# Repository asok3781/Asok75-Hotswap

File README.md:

# Asok75v2-Hotswap
This is a PCB designed to fit in the TX75v2 and be a replacement PCB for this keyboard, integrating Kailh hotswap sockets into the board.

This PCB uses [QMK firmware](https://github.com/asok3781/qmk_firmware/tree/asok/keyboards/asok/asok75hs) and a [VIA definition](asok75hsViaDefinition) has also been created to easily customise the layout of the keyboard.

This PCB uses QMK compatible side-firing LEDs to keep the underglow of the original PCB bright.

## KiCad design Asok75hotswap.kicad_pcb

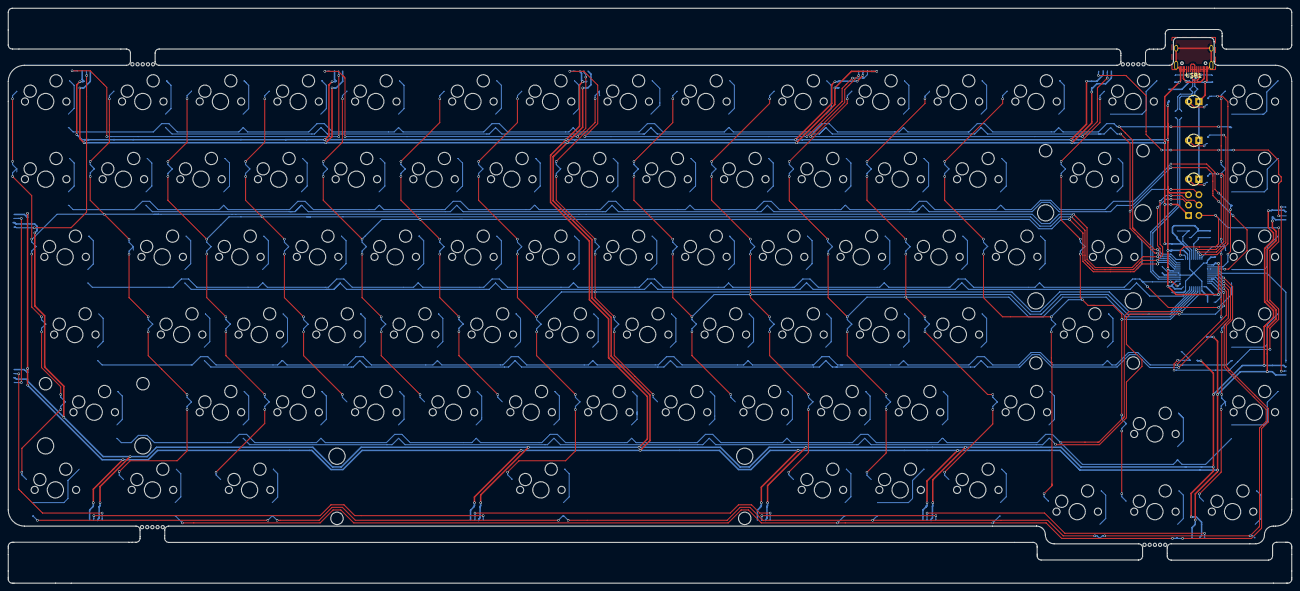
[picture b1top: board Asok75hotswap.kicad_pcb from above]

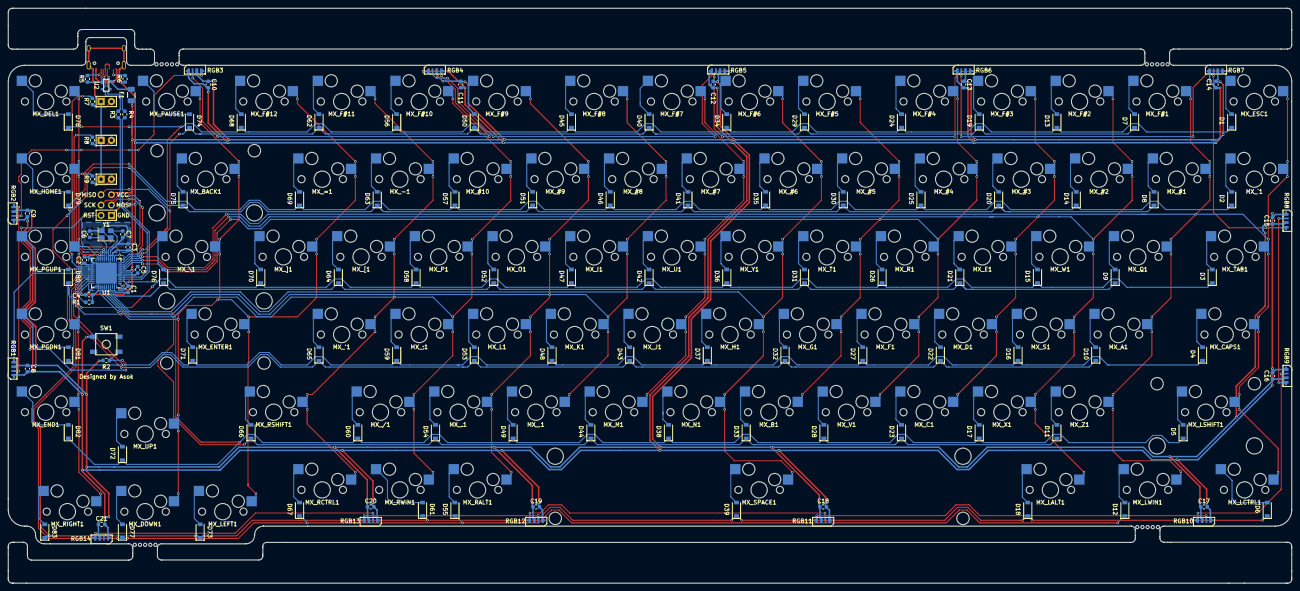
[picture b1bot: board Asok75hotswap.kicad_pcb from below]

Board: 2 copper layers, 314.8 x 141.0 mm, 224 parts (133 on the bottom side), 137 nets.

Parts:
C1: 10uF; C_0603_1608Metric
C2, C3, C4, C8, C9, C10, C11, C12, C13, C14, C15, C16, C17, C18, C19, C20, C21: 0.1uF; C_0603_1608Metric
C5: 1uF; C_0603_1608Metric
C6, C7: 22pF; C_0603_1608Metric
D1, D2, D3, D4, D5, D6, D7, D8, D9, D10, D11, D12, D13, D14, D15, D16, D17, D18, D19, D20, D21, D22, D23, D24, D25, D26, D27, D28, D29, D30, D31, D32, D33, D34, D35, D36, D37, D38, D39, D40, D41, D42, D43, D44, D45, D46, D47, D48, D49, D50, D51, D52, D53, D54, D55, D56, D57, D58, D59, D60, D61, D62, D63, D64, D65, D66, D67, D68, D69, D70, D71, D72, D73, D74, D75, D76, D77, D78, D79, D80, D81, D82, D83: SOD-123; D_SOD-123-Pretty
F1: 500mA; Fuse_1206_3216Metric
J1: AVR-ISP-6; Reset_Pretty-Mask
LED1, LED2, LED3: LED_Small; LED_D3.0mm-Pretty
MX_#1, MX_#2, MX_#3, MX_#4, MX_#5, MX_#6, MX_#7, MX_#8, MX_#9, MX_#10: MX-LED; MXOnly-1U-Hotswap
MX_'1: MX-LED; MXOnly-1U-Hotswap
MX_,1: MX-LED; MXOnly-1U-Hotswap
MX_-1: MX-LED; MXOnly-1U-Hotswap
MX_.1: MX-LED; MXOnly-1U-Hotswap
MX_/1: MX-LED; MXOnly-1U-Hotswap
MX_;1: MX-LED; MXOnly-1U-Hotswap
MX_=1: MX-LED; MXOnly-1U-Hotswap
MX_A1: MX-LED; MXOnly-1U-Hotswap
MX_B1: MX-LED; MXOnly-1U-Hotswap
MX_BACK1: MX-LED; MXOnly-2U-Hotswap
MX_C1: MX-LED; MXOnly-1U-Hotswap
MX_CAPS1: MX-LED; MXOnly-1.75U-Hotswap
MX_D1: MX-LED; MXOnly-1U-Hotswap
MX_DEL1: MX-LED; MXOnly-1U-Hotswap
MX_DOWN1: MX-LED; MXOnly-1U-Hotswap
MX_E1: MX-LED; MXOnly-1U-Hotswap
MX_END1: MX-LED; MXOnly-1U-Hotswap
MX_ENTER1: MX-LED; MXOnly-2.25U-Hotswap-ReversedStabilizers
MX_ESC1: MX-LED; MXOnly-1U-Hotswap
MX_F1: MX-LED; MXOnly-1U-Hotswap
MX_F#1, MX_F#2, MX_F#3, MX_F#4, MX_F#5, MX_F#6, MX_F#7, MX_F#8, MX_F#9, MX_F#10, MX_F#11, MX_F#12: MX-LED; MXOnly-1U-Hotswap
MX_G1: MX-LED; MXOnly-1U-Hotswap
MX_H1: MX-LED; MXOnly-1U-Hotswap
MX_HOME1: MX-LED; MXOnly-1U-Hotswap
MX_I1: MX-LED; MXOnly-1U-Hotswap
MX_J1: MX-LED; MXOnly-1U-Hotswap
MX_K1: MX-LED; MXOnly-1U-Hotswap
MX_L1: MX-LED; MXOnly-1U-Hotswap
MX_LALT1: MX-LED; MXOnly-1.25U-Hotswap
MX_LCTRL1: MX-LED; MXOnly-1.25U-Hotswap
MX_LEFT1: MX-LED; MXOnly-1U-Hotswap
MX_LSHIFT1: MX-LED; MXOnly-2.25U-Hotswap
MX_LWIN1: MX-LED; MXOnly-1.25U-Hotswap
MX_M1: MX-LED; MXOnly-1U-Hotswap
MX_N1: MX-LED; MXOnly-1U-Hotswap
MX_O1: MX-LED; MXOnly-1U-Hotswap
MX_P1: MX-LED; MXOnly-1U-Hotswap
MX_PAUSE1: MX-LED; MXOnly-1U-Hotswap
MX_PGDN1: MX-LED; MXOnly-1U-Hotswap
MX_PGUP1: MX-LED; MXOnly-1U-Hotswap
MX_Q1: MX-LED; MXOnly-1U-Hotswap
MX_R1: MX-LED; MXOnly-1U-Hotswap
MX_RALT1: MX-LED; MXOnly-1U-Hotswap
MX_RCTRL1: MX-LED; MXOnly-1U-Hotswap
MX_RIGHT1: MX-LED; MXOnly-1U-Hotswap
MX_RSHIFT1: MX-LED; MXOnly-1.75U-Hotswap
MX_RWIN1: MX-LED; MXOnly-1U-Hotswap
MX_S1: MX-LED; MXOnly-1U-Hotswap
MX_SPACE1: MX-LED; MXOnly-6.25U-Hotswap-ReversedStabilizers
MX_T1: MX-LED; MXOnly-1U-Hotswap
MX_TAB1: MX-LED; MXOnly-1.5U-Hotswap
MX_U1: MX-LED; MXOnly-1U-Hotswap
MX_UP1: MX-LED; MXOnly-1U-Hotswap
MX_V1: MX-LED; MXOnly-1U-Hotswap
MX_W1: MX-LED; MXOnly-1U-Hotswap
MX_X1: MX-LED; MXOnly-1U-Hotswap
MX_Y1: MX-LED; MXOnly-1U-Hotswap
MX_Z1: MX-LED; MXOnly-1U-Hotswap
MX_[1: MX-LED; MXOnly-1U-Hotswap
MX_\1: MX-LED; MXOnly-1.5U-Hotswap
MX_]1: MX-LED; MXOnly-1U-Hotswap
MX_`1: MX-LED; MXOnly-1U-Hotswap
R1, R2: 10K; R_0603_1608Metric
R3, R4: 22; R_0603_1608Metric
R5, R6: 5.1K; R_0603_1608Metric
R7, R8, R9: 1K; R_0603_1608Metric
RGB1, RGB2, RGB3, RGB4, RGB5, RGB6, RGB7, RGB8, RGB9, RGB10, RGB11, RGB12, RGB13, RGB14: SK6812-SIDEA-4020
SW1: SW_Push; SKQG-1155865
Tab1, Tab2, Tab3, Tab4: BreakawayTabs; breakaway-mousebites
U1: ATmega32U4-MU; QFN-44-1EP_7x7mm_P0.5mm_EP5.2x5.2mm
U2: PRTR5V0U2X; SOT143B
USB1: HRO-TYPE-C-31-M-12; HRO-TYPE-C-31-M-12-Assembly
Y1: 16MHz; Crystal_SMD_3225-4Pin_3.2x2.5mm

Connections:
+5V: C1.1, C2.1, C3.1, C4.1, C8.1, C9.1, C10.1, C11.1, C12.1, C13.1, C14.1, C15.1, C16.1, C17.1, C18.1, C19.1, C20.1, C21.1, F1.1, J1.2, R2.1, RGB1.2, RGB2.2, RGB3.2, RGB4.2, RGB5.2, RGB6.2, RGB7.2, RGB8.2, RGB9.2, RGB10.2, RGB11.2, RGB12.2, RGB13.2, RGB14.2, U1.2, U1.7, U1.14, U1.24, U1.34, U1.44
COL0: J1.4, MX_#1.1, MX_A1.1, MX_CAPS1.1, MX_ESC1.1, MX_F#1.1, MX_LCTRL1.1, MX_LSHIFT1.1, MX_LWIN1.1, MX_Q1.1, MX_TAB1.1, MX_Z1.1, MX_`1.1, U1.10
COL1: J1.3, MX_#2.1, MX_#3.1, MX_C1.1, MX_D1.1, MX_E1.1, MX_F#2.1, MX_F#3.1, MX_LALT1.1, MX_S1.1, MX_W1.1, MX_X1.1, U1.9
COL2: MX_#4.1, MX_#5.1, MX_B1.1, MX_F1.1, MX_F#4.1, MX_F#5.1, MX_G1.1, MX_R1.1, MX_T1.1, MX_V1.1, U1.8
COL3: MX_#6.1, MX_#7.1, MX_F#6.1, MX_F#7.1, MX_H1.1, MX_J1.1, MX_M1.1, MX_N1.1, MX_SPACE1.1, MX_U1.1, MX_Y1.1, U1.40
COL4: MX_#8.1, MX_#9.1, MX_,1.1, MX_.1.1, MX_F#8.1, MX_F#9.1, MX_I1.1, MX_K1.1, MX_L1.1, MX_O1.1, MX_RALT1.1, U1.39
COL5: MX_#10.1, MX_'1.1, MX_-1.1, MX_/1.1, MX_;1.1, MX_F#10.1, MX_F#11.1, MX_P1.1, MX_RCTRL1.1, MX_RSHIFT1.1, MX_RWIN1.1, MX_[1.1, U1.38
COL6: MX_=1.1, MX_BACK1.1, MX_DOWN1.1, MX_ENTER1.1, MX_F#12.1, MX_LEFT1.1, MX_PAUSE1.1, MX_UP1.1, MX_\1.1, MX_]1.1, U1.37
COL7: MX_DEL1.1, MX_END1.1, MX_HOME1.1, MX_PGDN1.1, MX_PGUP1.1, MX_RIGHT1.1, U1.21
D+: R3.1, U1.4
D-: R4.1, U1.3
GND: C1.2, C2.2, C3.2, C4.2, C5.2, C6.2, C7.2, C8.2, C9.2, C10.2, C11.2, C12.2, C13.2, C14.2, C15.2, C16.2, C17.2, C18.2, C19.2, C20.2, C21.2, J1.6, LED1.1, LED2.1, LED3.1, R1.1, R5.1, R6.1, RGB1.4, RGB2.4, RGB3.4, RGB4.4, RGB5.4, RGB6.4, RGB7.4, RGB8.4, RGB9.4, RGB10.4, RGB11.4, RGB12.4, RGB13.4, RGB14.4, SW1.1, U1.5, U1.15, U1.23, U1.35, U1.43, U1.45, U2.1, USB1.1, USB1.12, USB1.13, Y1.2, Y1.4
LEDIND1: R7.2, U1.20
LEDIND2: R8.2, U1.19
LEDIND3: R9.2, U1.18
unnamed: C5.1, U1.6
unnamed: C6.1, U1.17, Y1.1
unnamed: C7.1, U1.16, Y1.3
unnamed: D1.2, MX_ESC1.2
unnamed: D2.2, MX_`1.2
unnamed: D3.2, MX_TAB1.2
unnamed: D4.2, MX_CAPS1.2
unnamed: D5.2, MX_LSHIFT1.2
unnamed: D6.2, MX_LCTRL1.2
unnamed: D7.2, MX_F#1.2
unnamed: D8.2, MX_#1.2
unnamed: D9.2, MX_Q1.2
unnamed: D10.2, MX_A1.2
unnamed: D11.2, MX_Z1.2
unnamed: D12.2, MX_LWIN1.2
unnamed: D13.2, MX_F#2.2
unnamed: D14.2, MX_#2.2
unnamed: D15.2, MX_W1.2
unnamed: D16.2, MX_S1.2
unnamed: D17.2, MX_X1.2
unnamed: D18.2, MX_LALT1.2
unnamed: D19.2, MX_F#3.2
unnamed: D20.2, MX_#3.2
unnamed: D21.2, MX_E1.2
unnamed: D22.2, MX_D1.2
unnamed: D23.2, MX_C1.2
unnamed: D24.2, MX_F#4.2
unnamed: D25.2, MX_#4.2
unnamed: D26.2, MX_R1.2
unnamed: D27.2, MX_F1.2
unnamed: D28.2, MX_V1.2
unnamed: D29.2, MX_F#5.2
unnamed: D30.2, MX_#5.2
unnamed: D31.2, MX_T1.2
unnamed: D32.2, MX_G1.2
unnamed: D33.2, MX_B1.2
unnamed: D34.2, MX_F#6.2
unnamed: D35.2, MX_#6.2
unnamed: D36.2, MX_Y1.2
unnamed: D37.2, MX_H1.2
unnamed: D38.2, MX_N1.2
unnamed: D39.2, MX_SPACE1.2
unnamed: D40.2, MX_F#7.2
unnamed: D41.2, MX_#7.2
unnamed: D42.2, MX_U1.2
unnamed: D43.2, MX_J1.2
unnamed: D44.2, MX_M1.2
unnamed: D45.2, MX_F#8.2
unnamed: D46.2, MX_#8.2
unnamed: D47.2, MX_I1.2
unnamed: D48.2, MX_K1.2
unnamed: D49.2, MX_,1.2
unnamed: D50.2, MX_F#9.2
unnamed: D51.2, MX_#9.2
unnamed: D52.2, MX_O1.2
unnamed: D53.2, MX_L1.2
unnamed: D54.2, MX_.1.2
unnamed: D55.2, MX_RALT1.2
unnamed: D56.2, MX_F#10.2
unnamed: D57.2, MX_#10.2
unnamed: D58.2, MX_P1.2
unnamed: D59.2, MX_;1.2
unnamed: D60.2, MX_/1.2
unnamed: D61.2, MX_RWIN1.2
unnamed: D62.2, MX_F#11.2
unnamed: D63.2, MX_-1.2
unnamed: D64.2, MX_[1.2
unnamed: D65.2, MX_'1.2
unnamed: D66.2, MX_RSHIFT1.2
unnamed: D67.2, MX_RCTRL1.2
unnamed: D68.2, MX_F#12.2
unnamed: D69.2, MX_=1.2
unnamed: D70.2, MX_]1.2
unnamed: D71.2, MX_ENTER1.2
unnamed: D72.2, MX_UP1.2
unnamed: D73.2, MX_LEFT1.2
unnamed: D74.2, MX_PAUSE1.2
unnamed: D75.2, MX_BACK1.2
unnamed: D76.2, MX_\1.2
unnamed: D77.2, MX_DOWN1.2
unnamed: D78.2, MX_DEL1.2
unnamed: D79.2, MX_HOME1.2
unnamed: D80.2, MX_PGUP1.2
unnamed: D81.2, MX_PGDN1.2
unnamed: D82.2, MX_END1.2
unnamed: D83.2, MX_RIGHT1.2
unnamed: LED1.2, R7.1
unnamed: LED2.2, R8.1
unnamed: LED3.2, R9.1
unnamed: R1.2, U1.33
unnamed: R3.2, U2.2, USB1.6, USB1.8
unnamed: R4.2, U2.3, USB1.5, USB1.7
unnamed: R5.2, USB1.4
unnamed: R6.2, USB1.10
unnamed: RGB1.3, RGB2.1
unnamed: RGB2.3, RGB3.1
unnamed: RGB3.3, RGB4.1
unnamed: RGB4.3, RGB5.1
unnamed: RGB5.3, RGB6.1
unnamed: RGB6.3, RGB7.1
unnamed: RGB7.3, RGB8.1
unnamed: RGB8.3, RGB9.1
unnamed: RGB9.3, RGB10.1
unnamed: RGB10.3, RGB11.1
unnamed: RGB11.3, RGB12.1
unnamed: RGB12.3, RGB13.1
unnamed: RGB13.3, RGB14.1
RESET: J1.5, R2.2, SW1.2, U1.13
RGBLED: RGB1.1, U1.27
ROW0: D1.1, D13.1, D24.1, D34.1, D45.1, D56.1, D68.1, D78.1, U1.12
ROW1: D7.1, D19.1, D29.1, D40.1, D50.1, D62.1, D74.1, J1.1, U1.11
ROW2: D2.1, D14.1, D25.1, D35.1, D46.1, D57.1, D69.1, D79.1, U1.25
ROW3: D8.1, D20.1, D30.1, D41.1, D51.1, D63.1, D75.1, U1.26
ROW4: D3.1, D15.1, D26.1, D36.1, D47.1, D58.1, D70.1, D80.1, U1.1
ROW5: D9.1, D21.1, D31.1, D42.1, D52.1, D64.1, D76.1, U1.41
ROW6: D4.1, D16.1, D27.1, D37.1, D48.1, D59.1, D71.1, D81.1, U1.31
ROW7: D10.1, D22.1, D32.1, D43.1, D53.1, D65.1, U1.30
ROW8: D5.1, D17.1, D28.1, D38.1, D49.1, D60.1, D72.1, D82.1, U1.36
ROW9: D11.1, D23.1, D33.1, D44.1, D54.1, D66.1, U1.32
ROW10: D6.1, D18.1, D39.1, D61.1, D73.1, D83.1, U1.29
ROW11: D12.1, D55.1, D67.1, D77.1, U1.28
VCC: F1.2, U2.4, USB1.2, USB1.11

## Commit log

2020-08-04 Reorganised folders and placed RGB LEDs on hotswap pcb
2020-08-11 Removed extra symbols in schematic in hotswap variant
2020-08-12 Updated PCB dimensions and component placement on hotswap variant
2020-08-14 Updated underglow LED footprint
2020-08-17 Routed USB and MCU area for hotswap version
2020-08-18 Updated edge cuts
2020-08-18 Updated hotswap PCB
2020-08-19 Completed routing rows, MCU and USB
2020-08-19 Finished routing columns in hotswap version
2020-08-20 Routed underglow LEDs
2020-08-20 Finished routing underglow LED power traces
2020-08-22 Finished routing hotswap version
2020-09-12 Moved case folder to be with v1 PCB
2020-09-21 Refactored project into two separate repositories
2020-09-21 Added VIA definition to repository
